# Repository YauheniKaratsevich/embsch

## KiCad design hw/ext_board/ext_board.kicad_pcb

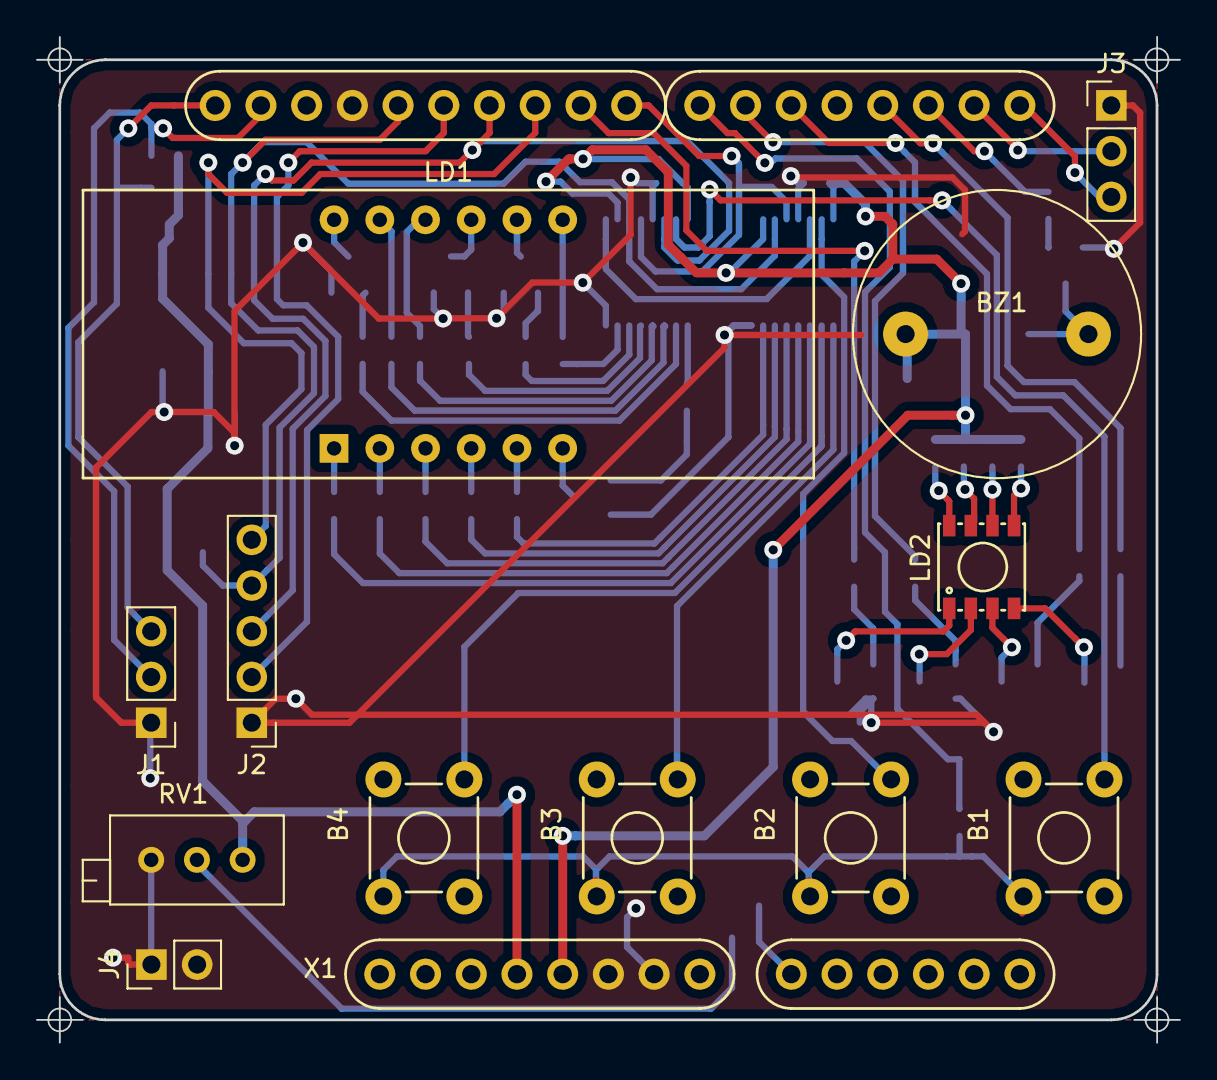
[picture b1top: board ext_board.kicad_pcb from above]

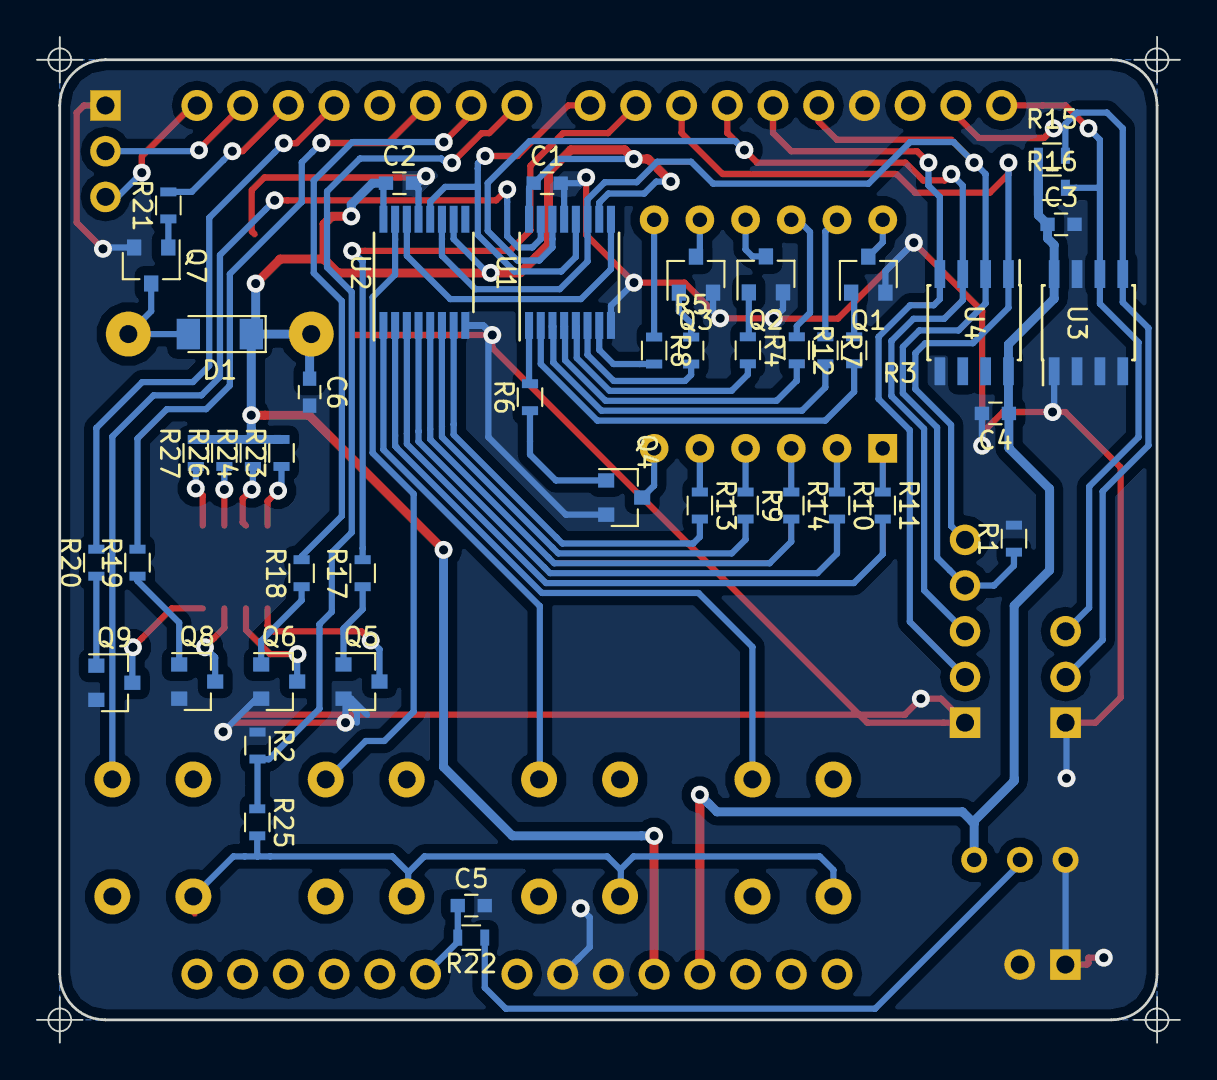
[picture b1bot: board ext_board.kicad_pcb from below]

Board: 2 copper layers, 63.5 x 55.8 mm, 60 parts (47 on the bottom side), 68 nets.

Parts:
B1, B2, B3, B4: IT_1102WB_6x6x7; KLS7-TS6601_6x6x4.3
BZ1: Buzzer; BUZZER_10_16d
C1, C2, C3, C4, C5, C6: 100n; C0603
D1: LL4148; D_MiniMELF
J1, J3: Conn_01x03; Pin_Header_Straight_1x03_Pitch2.54mm
J2: Conn_01x05; Pin_Header_Straight_1x05_Pitch2.54mm
J4: Conn_01x02; Pin_Header_Straight_1x02_Pitch2.54mm
LD1: GNQ-4041AS
LD2: RGBW; GNL-5050WRGB
Q1, Q2, Q3, Q4, Q5, Q6, Q7, Q8, Q9: SS8050; SOT-23
R1, R2: 10k; R0603
R3, R4, R5, R6, R15, R16, R17, R18, R19, R20, R21: 4.7k; R0603
R7, R8, R9, R10, R11, R12, R13, R14, R23, R24, R26, R27: R; R0603
R22: 1k; R0603
R25: 6.8k; R0603
RV1: 10k; Potentiometer_Trimmer_Bourns_3296X
U1, U2: 74HC595PW; TSSOP-16_4.4x5mm_Pitch0.65mm
U3: M24LC16; SOIC-8_3.9x4.9mm_Pitch1.27mm
U4: M93C76; SOIC-8_3.9x4.9mm_Pitch1.27mm
X1: UNO_R3_CONN

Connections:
+3V3: C3.1, C4.1, R15.1, R16.1, RV1.1, U3.8, U4.8, X1.4
+5V: BZ1.1, C1.1, C2.1, C6.1, D1.1, R23.2, R24.2, R26.2, R27.2, U1.10, U1.16, U2.10, U2.16, X1.5
/ADC: C5.1, R22.2, X1.9
/CLK: J1.3, R16.2, U3.6, X1.32
/KEY: R2.2, R25.1, X1.22
/KEY_B1: B1.4, U1.15
/KEY_B2: B2.4, U2.15
/KEY_B3: B3.4, U2.1
/KEY_B4: B4.4, U2.2
/LEDB: R18.2, X1.21
/LEDG: R19.2, X1.20
/LEDR: R20.2, X1.18
/LEDW: R17.2, X1.24
/LED_1: R3.2, U1.2
/LED_2: R4.2, U1.5
/LED_3: R5.2, U1.6
/LED_4: R6.2, U1.1
/LED_A: R7.2, U1.3
/LED_B: R8.2, U1.7
/LED_C: R9.2, U2.6
/LED_D: R10.2, U2.4
/LED_DP: R14.2, U2.5
/LED_E: R11.2, U2.3
/LED_F: R12.2, U1.4
/LED_G: R13.2, U2.7
/MISO: J2.2, U4.4, X1.27
/MOSI: J2.3, U1.14, U4.3, X1.26
/PWM: R21.2, X1.17
/RCLK: U1.12, U2.12, X1.23
/RX: J3.3, X1.15
/SCK: J2.4, R1.1, U1.11, U2.11, U4.2, X1.28
/SDA: J1.2, R15.2, U3.5, X1.31
/TX: J3.2, X1.16
/~CS: J2.5, U4.1, X1.25
GND: C1.2, C2.2, C3.2, C4.2, C5.2, C6.2, J1.1, J2.1, J3.1, J4.1, J4.2, Q1.2, Q2.2, Q3.2, Q4.2, Q5.2, Q6.2, Q7.2, Q8.2, Q9.2, R1.2, R2.1, RV1.3, U1.8, U1.13, U2.8, U2.13, U3.1, U3.2, U3.3, U3.4, U3.7, U4.5, X1.6, X1.7, X1.29
unnamed: B1.1, B2.1, B3.1, B4.1, R25.2
unnamed: BZ1.2, D1.2, Q7.3
unnamed: LD1.1, R11.1
unnamed: LD1.2, R10.1
unnamed: LD1.3, R14.1
unnamed: LD1.4, R9.1
unnamed: LD1.5, R13.1
unnamed: LD1.6, Q4.3
unnamed: LD1.7, R8.1
unnamed: LD1.8, Q3.3
unnamed: LD1.9, Q2.3
unnamed: LD1.10, R12.1
unnamed: LD1.11, R7.1
unnamed: LD1.12, Q1.3
unnamed: LD2.1, Q5.3
unnamed: LD2.2, Q6.3
unnamed: LD2.3, Q8.3
unnamed: LD2.4, Q9.3
unnamed: LD2.5, R27.1
unnamed: LD2.6, R26.1
unnamed: LD2.7, R24.1
unnamed: LD2.8, R23.1
unnamed: Q1.1, R3.1
unnamed: Q2.1, R4.1
unnamed: Q3.1, R5.1
unnamed: Q4.1, R6.1
unnamed: Q5.1, R17.1
unnamed: Q6.1, R18.1
unnamed: Q7.1, R21.1
unnamed: Q8.1, R19.1
unnamed: Q9.1, R20.1
unnamed: R22.1, RV1.2
unnamed: U1.9, U2.14

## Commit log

2019-07-06 Add initial repo structure
2019-07-06 Add questions
2019-07-06 Add schematic and lib
2019-07-23 Add some ideas for 01 lecture
2019-08-11 Add slide for lecture 01
2019-09-14 Add components
2019-09-15 Add layout
2019-09-16 Change buttons to TH
2019-09-18 Add reference signes
2019-09-21 Remove useless via
2019-12-22 Add diodes to buttons
